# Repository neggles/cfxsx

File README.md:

# cfxsx

Xbox Series X/S storage expansion card to M.2 NGFF NVMe SSD adapter. Well, maybe.

The connector the X/S use is CFexpress-adjacent - I have _no idea_ if this will even begin to work, but, YOLO?

# But, for real, don't make this. It probably doesn't work at all.

## Repository Structure
- `cfxsx` contains the main schematics and board drawing
- `cfxsx/PCIexpress.pretty` contains the board-specific footprints
- `cfxsx/PCIexpress.3dshapes` contains the 3D models for parts on the board (and a bunch of extras from my various experiments)

## Building
Simply call `make` in the top-top level directory. The `build` directory will then contain:

- the main board
- zipped gerbers for the boards you can directly use for manufacturing
- zipped gerbers and SMT assembly BOM/position files for JLCPCB's SMT assembly service for the single-board version.

Makefile uses [Jan Mrázek](https://github.com/yaqwsx)'s [KiKit](https://github.com/yaqwsx/KiKit), which I cannot recommend enough, and therefore has to be available on your system.

Jan's [jlcparts](https://yaqwsx.github.io/jlcparts/) app was also extremely useful in narrowing down part choices based on what JLCPCB have available.

-----
### **IMPORTANT NOTE:** If you give JLCPCB these files as-is, *please* verify the orientation of every part before submitting.

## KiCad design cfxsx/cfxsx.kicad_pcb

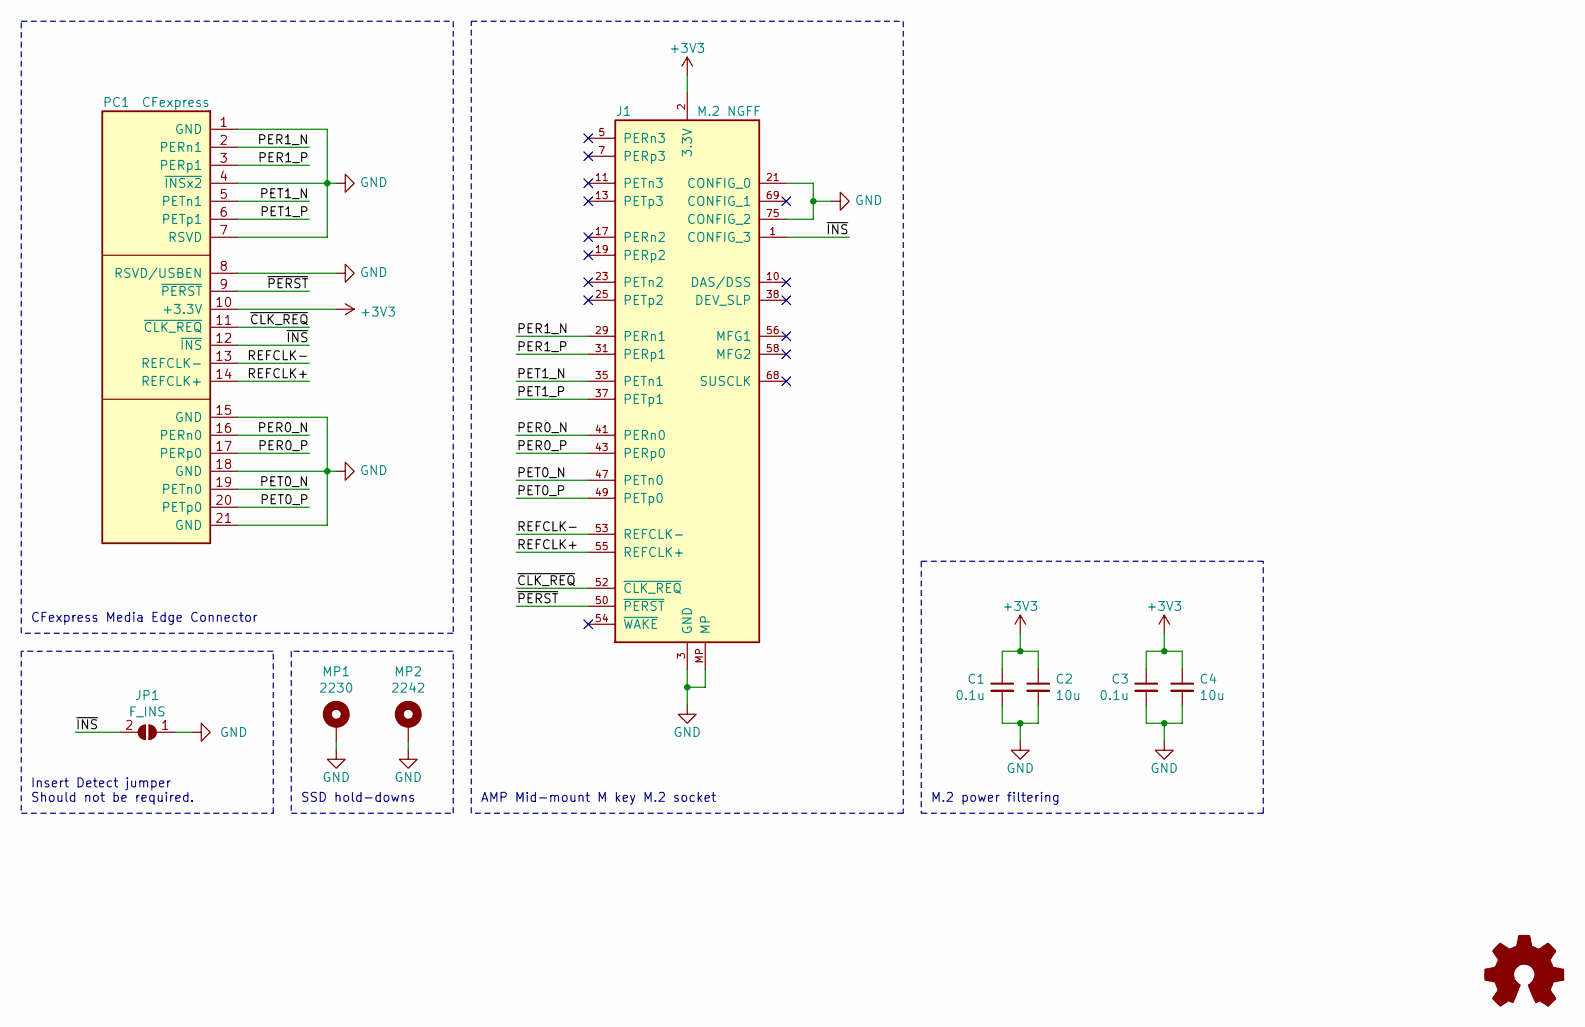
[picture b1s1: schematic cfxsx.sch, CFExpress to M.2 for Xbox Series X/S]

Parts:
C1, C3: 0.1u; C_0402_1005Metric_Pad0.74x0.62mm_HandSolder
C2, C4: 10u; C_0402_1005Metric_Pad0.74x0.62mm_HandSolder
J1: M.2 NGFF; AMP_MDT180xxx001_NGFF-KeyM; MPN MDT180M03001
JP1: F_INS; SolderJumper-2_P0.6mm_Open_RoundedPad1.0x1.5mm
MP1: 2230; MountingHole_NGFF_4.2mm_Pad_TopBottom
MP2: 2242; MountingHole_NGFF_4.2mm_Pad_TopBottom
PC1: CFexpress; CFExpress_Media
SYM1: logo; neggle-logo-0.12

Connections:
+3V3: C1.1, C2.1, C3.1, C4.1, J1.2 (3.3V), J1.4 (3.3V), J1.12 (3.3V), J1.14 (3.3V), J1.16 (3.3V), J1.18 (3.3V), J1.70 (3.3V), J1.72 (3.3V), J1.74 (3.3V), PC1.10 (+3.3V)
/PER0_N: J1.41 (PERn0), PC1.16 (PERn0)
/PER0_P: J1.43 (PERp0), PC1.17 (PERp0)
/PER1_N: J1.29 (PERn1), PC1.2 (PERn1)
/PER1_P: J1.31 (PERp1), PC1.3 (PERp1)
/PET0_N: J1.47 (PETn0), PC1.19 (PETn0)
/PET0_P: J1.49 (PETp0), PC1.20 (PETp0)
/PET1_N: J1.35 (PETn1), PC1.5 (PETn1)
/PET1_P: J1.37 (PETp1), PC1.6 (PETp1)
/REFCLK+: J1.55 (REFCLK+), PC1.14 (REFCLK+)
/REFCLK-: J1.53 (REFCLK-), PC1.13 (REFCLK-)
/~CLK_REQ: J1.52 (~CLK_REQ), PC1.11 (~CLK_REQ)
/~INS: J1.1 (CONFIG_3), JP1.2 (B), PC1.12 (~INS)
/~PERST: J1.50 (~PERST), PC1.9 (~PERST)
GND: C1.2, C2.2, C3.2, C4.2, J1.3 (GND), J1.9 (GND), J1.15 (GND), J1.21 (CONFIG_0), J1.27 (GND), J1.33 (GND), J1.39 (GND), J1.45 (GND), J1.51 (GND), J1.57 (GND), J1.71 (GND), J1.73 (GND), J1.75 (CONFIG_2), J1.MP, JP1.1 (A), MP1.1, MP2.1, PC1.1 (GND), PC1.4 (~INSx2), PC1.7 (RSVD), PC1.8 (RSVD/USBEN), PC1.15 (GND), PC1.18 (GND), PC1.21 (GND)

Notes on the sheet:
CFexpress Media Edge Connector
Insert Detect jumper Should not be required.
SSD hold-downs
AMP Mid-mount M key M.2 socket
M.2 power filtering

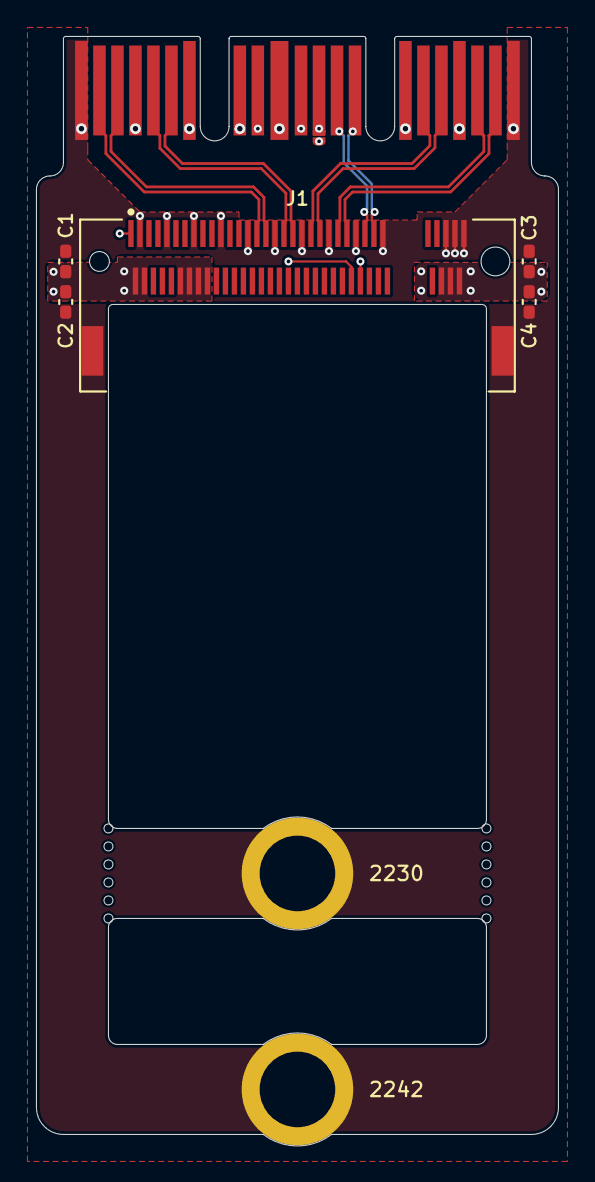
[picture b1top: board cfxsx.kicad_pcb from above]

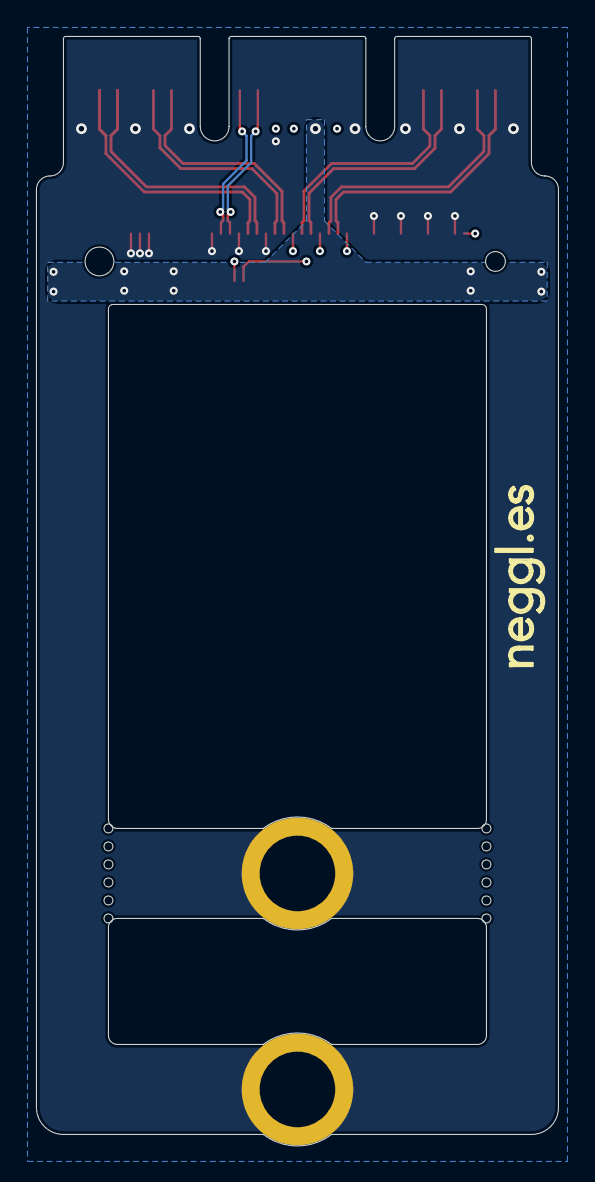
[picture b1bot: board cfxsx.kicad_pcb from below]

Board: 4 copper layers, 29.0 x 61.6 mm, 10 parts (3 on the bottom side), 15 nets.

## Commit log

2021-08-08 init
2021-08-08 add 2280
2021-08-08 Deploying to gh-pages from @ neg2led/cfxsx@9ed75ca86431fc5cdcf2469d1caaca7a0f178fc8 🚀
2021-08-08 Initial gh-pages commit
2021-08-08 Deploying to gh-pages from @ neg2led/cfxsx@5fded029270c65b2b62c4b467ed82b7d2456e2af 🚀
2021-08-08 fixup page title in makefile
2021-08-08 Deploying to gh-pages from @ neg2led/cfxsx@e9afefae46139b079a5741253e2b3ecd4c97877d 🚀
2021-08-08 add 2280 board to the makefile
2021-08-08 fix linkback in Pages
2021-08-08 helps to remember that the 2280 version is bigger
2021-08-08 Deploying to gh-pages from @ neg2led/cfxsx@4a3f01c83f23216ed0fae90ac7fff194f62540df 🚀
